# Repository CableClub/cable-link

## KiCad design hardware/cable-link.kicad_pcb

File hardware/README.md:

# Cable-Link Reference Hardware design

## Useful Links

* [Gerber Generation for PCBWay](https://www.pcbway.com/blog/help_center/Generate_Gerber_file_from_Kicad.html)
* [Position Generation for PCBWay](https://www.pcbway.com/blog/help_center/Generate_Position_File_in_Kicad.html)

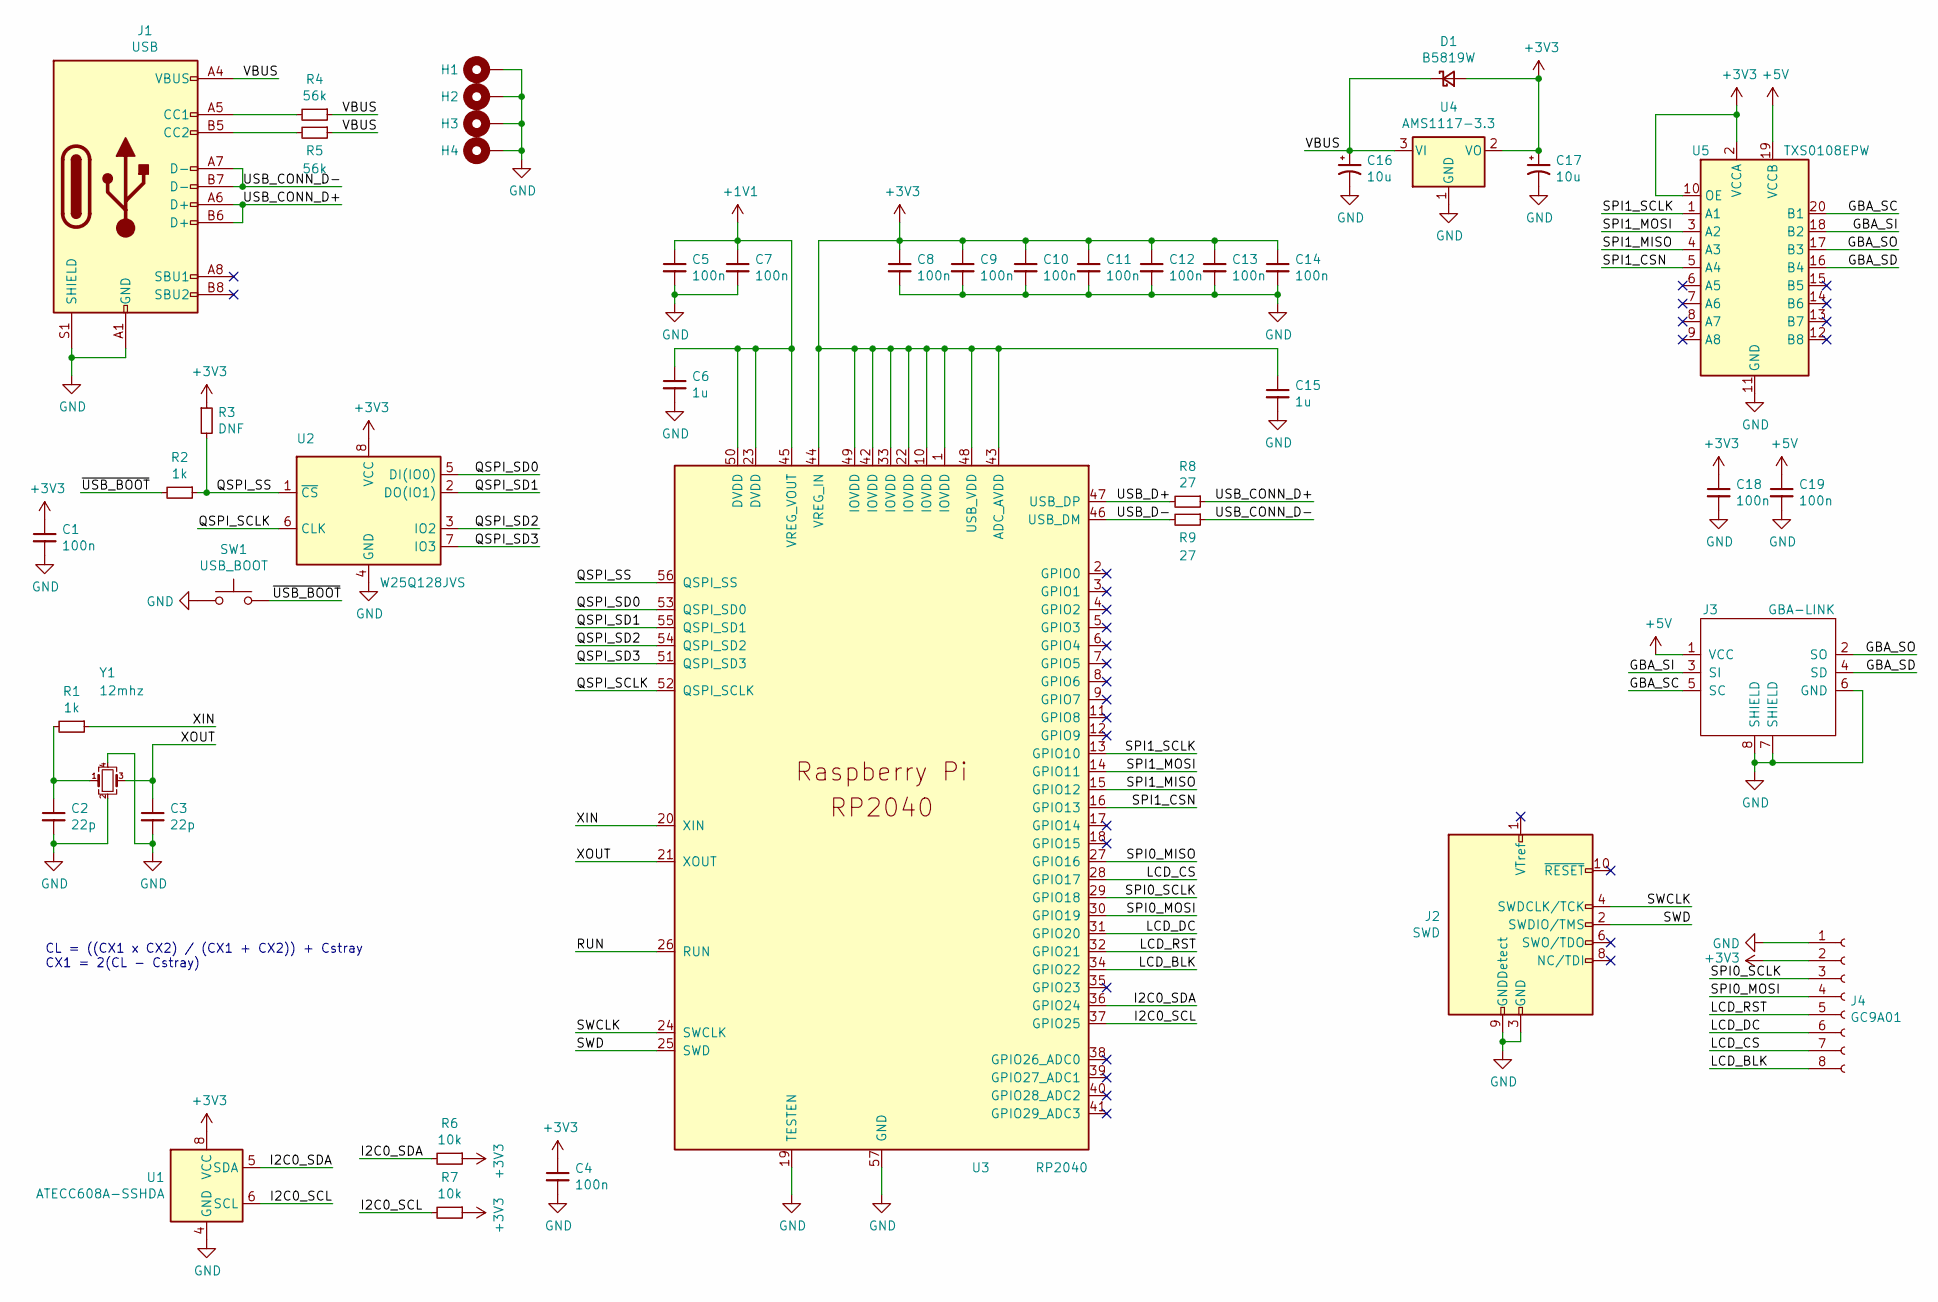
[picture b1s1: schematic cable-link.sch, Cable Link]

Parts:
C1, C4, C5, C7, C8, C9, C10, C11, C12, C13, C14, C18, C19: 100n; C_0402_1005Metric; LCSC_FP 0402
C2, C3: 22p; C_0402_1005Metric; LCSC_FP 0402
C6, C15: 1u; C_0402_1005Metric; LCSC_FP 0402
C16, C17: 10u; CP_EIA-3216-18_Kemet-A; LCSC_FP CASE-A_3216
D1: B5819W; D_SOD-123; LCSC_PN C8598
H1, H2, H3, H4: MountingHole_Pad; MountingHole_2.2mm_M2_DIN965_Pad
J1: USB; TYPE-C-31-M-12; LCSC_FP TYPE-C-31_L8.94_W7.3
J2: SWD; 20021221-00010C4LF
J3: GBA-LINK
J4: GC9A01; PinHeader_1x08_P2.54mm_Vertical
R1, R2: 1k; R_0402_1005Metric; LCSC_FP 0402
R3: DNF; R_0402_1005Metric
R4, R5: 56k; R_0402_1005Metric; LCSC_FP 0402
R6, R7: 10k; R_0402_1005Metric; LCSC_FP 0402
R8, R9: 27; R_0402_1005Metric; LCSC_FP 0402
SW1: USB_BOOT; SW_Push_1P1T_NO_6x6mm_H9.5mm; LCSC_FP SMD-4
U1: ATECC608A-SSHDA; SOIC-8_3.9x4.9mm_P1.27mm; LCSC_FP SOIC-8_3.9x4.9x1.27P
U2: W25Q128JVS; SOIC-8_5.23x5.23mm_P1.27mm; LCSC_FP SOIC-8_5.3x5.3x1.27P
U3: RP2040; RP2040-QFN-56; LCSC_FP LQFN-56_EP_7.0x7.0x0.4P
U4: AMS1117-3.3; SOT-223-3_TabPin2; LCSC_FP SOT-223
U5: TXS0108EPW; TSSOP-20_4.4x6.5mm_P0.65mm; LCSC_FP TSSOP-20_4.4x6.5x0.65P
Y1: 12mhz; Crystal_SMD_3225-4Pin_3.2x2.5mm; LCSC_FP SMD-3225_4P

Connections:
+1V1: C5.1, C6.1, C7.1, U3.23 (DVDD), U3.45 (VREG_VOUT), U3.50 (DVDD)
+3V3: C1.1, C4.1, C8.1, C9.1, C10.1, C11.1, C12.1, C13.1, C14.1, C15.1, C17.1, C18.1, D1.2 (A), J4.2, R3.1, R6.1, R7.1, U1.8 (VCC), U2.8 (VCC), U3.1 (IOVDD), U3.10 (IOVDD), U3.22 (IOVDD), U3.33 (IOVDD), U3.42 (IOVDD), U3.43 (ADC_AVDD), U3.44 (VREG_IN), U3.48 (USB_VDD), U3.49 (IOVDD), U4.2 (VO), U5.2 (VCCA), U5.10 (OE)
+5V: C19.1, J3.1 (VCC), U5.19 (VCCB)
/GBA_SC: J3.5 (SC), U5.20 (B1)
/GBA_SD: J3.4 (SD), U5.16 (B4)
/GBA_SI: J3.3 (SI), U5.18 (B2)
/GBA_SO: J3.2 (SO), U5.17 (B3)
/I2C0_SCL: R7.2, U1.6 (SCL), U3.37 (GPIO25)
/I2C0_SDA: R6.2, U1.5 (SDA), U3.36 (GPIO24)
/LCD_BLK: J4.8, U3.34 (GPIO22)
/LCD_CS: J4.7, U3.28 (GPIO17)
/LCD_DC: J4.6, U3.31 (GPIO20)
/LCD_RST: J4.5, U3.32 (GPIO21)
/QSPI_SCLK: U2.6 (CLK), U3.52 (QSPI_SCLK)
/QSPI_SD0: U2.5 (DI(IO0)), U3.53 (QSPI_SD0)
/QSPI_SD1: U2.2 (DO(IO1)), U3.55 (QSPI_SD1)
/QSPI_SD2: U2.3 (IO2), U3.54 (QSPI_SD2)
/QSPI_SD3: U2.7 (IO3), U3.51 (QSPI_SD3)
/QSPI_SS: R2.1, R3.2, U2.1 (~CS), U3.56 (QSPI_SS)
/RUN: U3.26 (RUN)
/SPI0_MISO: U3.27 (GPIO16)
/SPI0_MOSI: J4.4, U3.30 (GPIO19)
/SPI0_SCLK: J4.3, U3.29 (GPIO18)
/SPI1_CSN: U3.16 (GPIO13), U5.5 (A4)
/SPI1_MISO: U3.15 (GPIO12), U5.4 (A3)
/SPI1_MOSI: U3.14 (GPIO11), U5.3 (A2)
/SPI1_SCLK: U3.13 (GPIO10), U5.1 (A1)
/SWCLK: J2.4 (SWDCLK/TCK), U3.24 (SWCLK)
/SWD: J2.2 (SWDIO/TMS), U3.25 (SWD)
/USB_CONN_D+: J1.A6 (D+), J1.B6 (D+), R8.1
/USB_CONN_D-: J1.A7 (D-), J1.B7 (D-), R9.1
/USB_D+: R8.2, U3.47 (USB_DP)
/USB_D-: R9.2, U3.46 (USB_DM)
/VBUS: C16.1, D1.1 (K), J1.A4 (VBUS), J1.A9 (VBUS), J1.B4 (VBUS), J1.B9 (VBUS), R4.1, R5.1, U4.3 (VI)
/XIN: R1.1, U3.20 (XIN)
/XOUT: C3.1, U3.21 (XOUT), Y1.3
/~USB_BOOT: R2.2, SW1.2
GND: C1.2, C2.2, C3.2, C4.2, C5.2, C6.2, C7.2, C8.2, C9.2, C10.2, C11.2, C12.2, C13.2, C14.2, C15.2, C16.2, C17.2, C18.2, C19.2, H1.1, H2.1, H3.1, H4.1, J1.A1 (GND), J1.A12 (GND), J1.B1 (GND), J1.B12 (GND), J1.S1 (SHIELD), J2.3 (GND), J2.5 (GND), J2.9 (GNDDetect), J3.6 (GND), J3.7 (SHIELD), J3.8 (SHIELD), J4.1, SW1.1, U1.4 (GND), U2.4 (GND), U3.19 (TESTEN), U3.57 (GND), U4.1 (GND), U5.11 (GND), Y1.2, Y1.4
unnamed: C2.1, R1.2, Y1.1
unnamed: J1.A5 (CC1), R4.2
unnamed: J1.B5 (CC2), R5.2

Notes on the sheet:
CL = ((CX1 x CX2) / (CX1 + CX2)) + Cstray CX1 = 2(CL - Cstray)

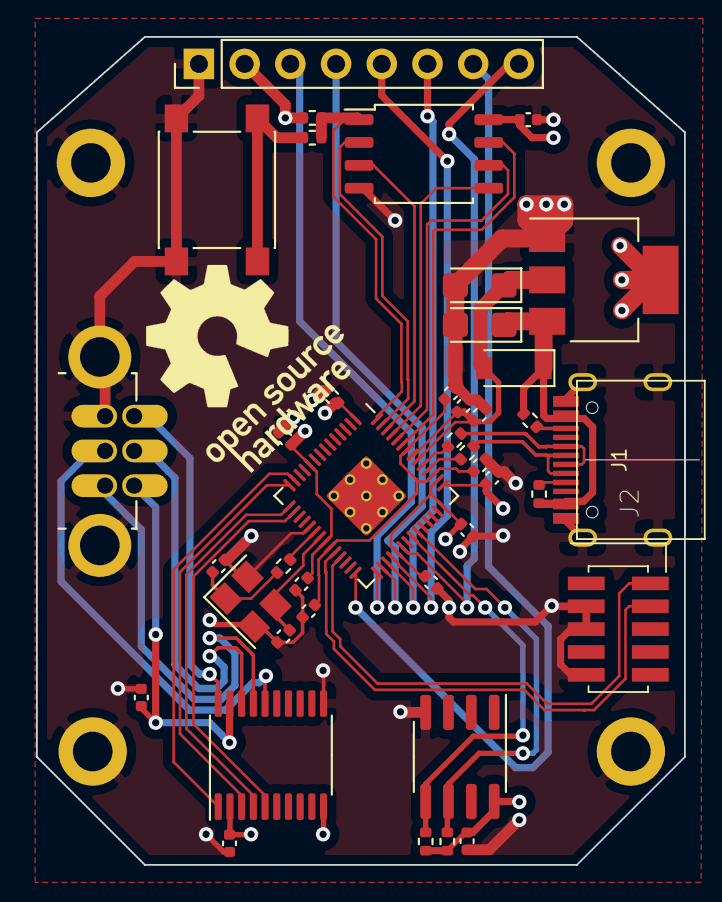
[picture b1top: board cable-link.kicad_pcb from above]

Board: 4 copper layers, 36.0 x 46.0 mm, 44 parts (0 on the bottom side), 39 nets.

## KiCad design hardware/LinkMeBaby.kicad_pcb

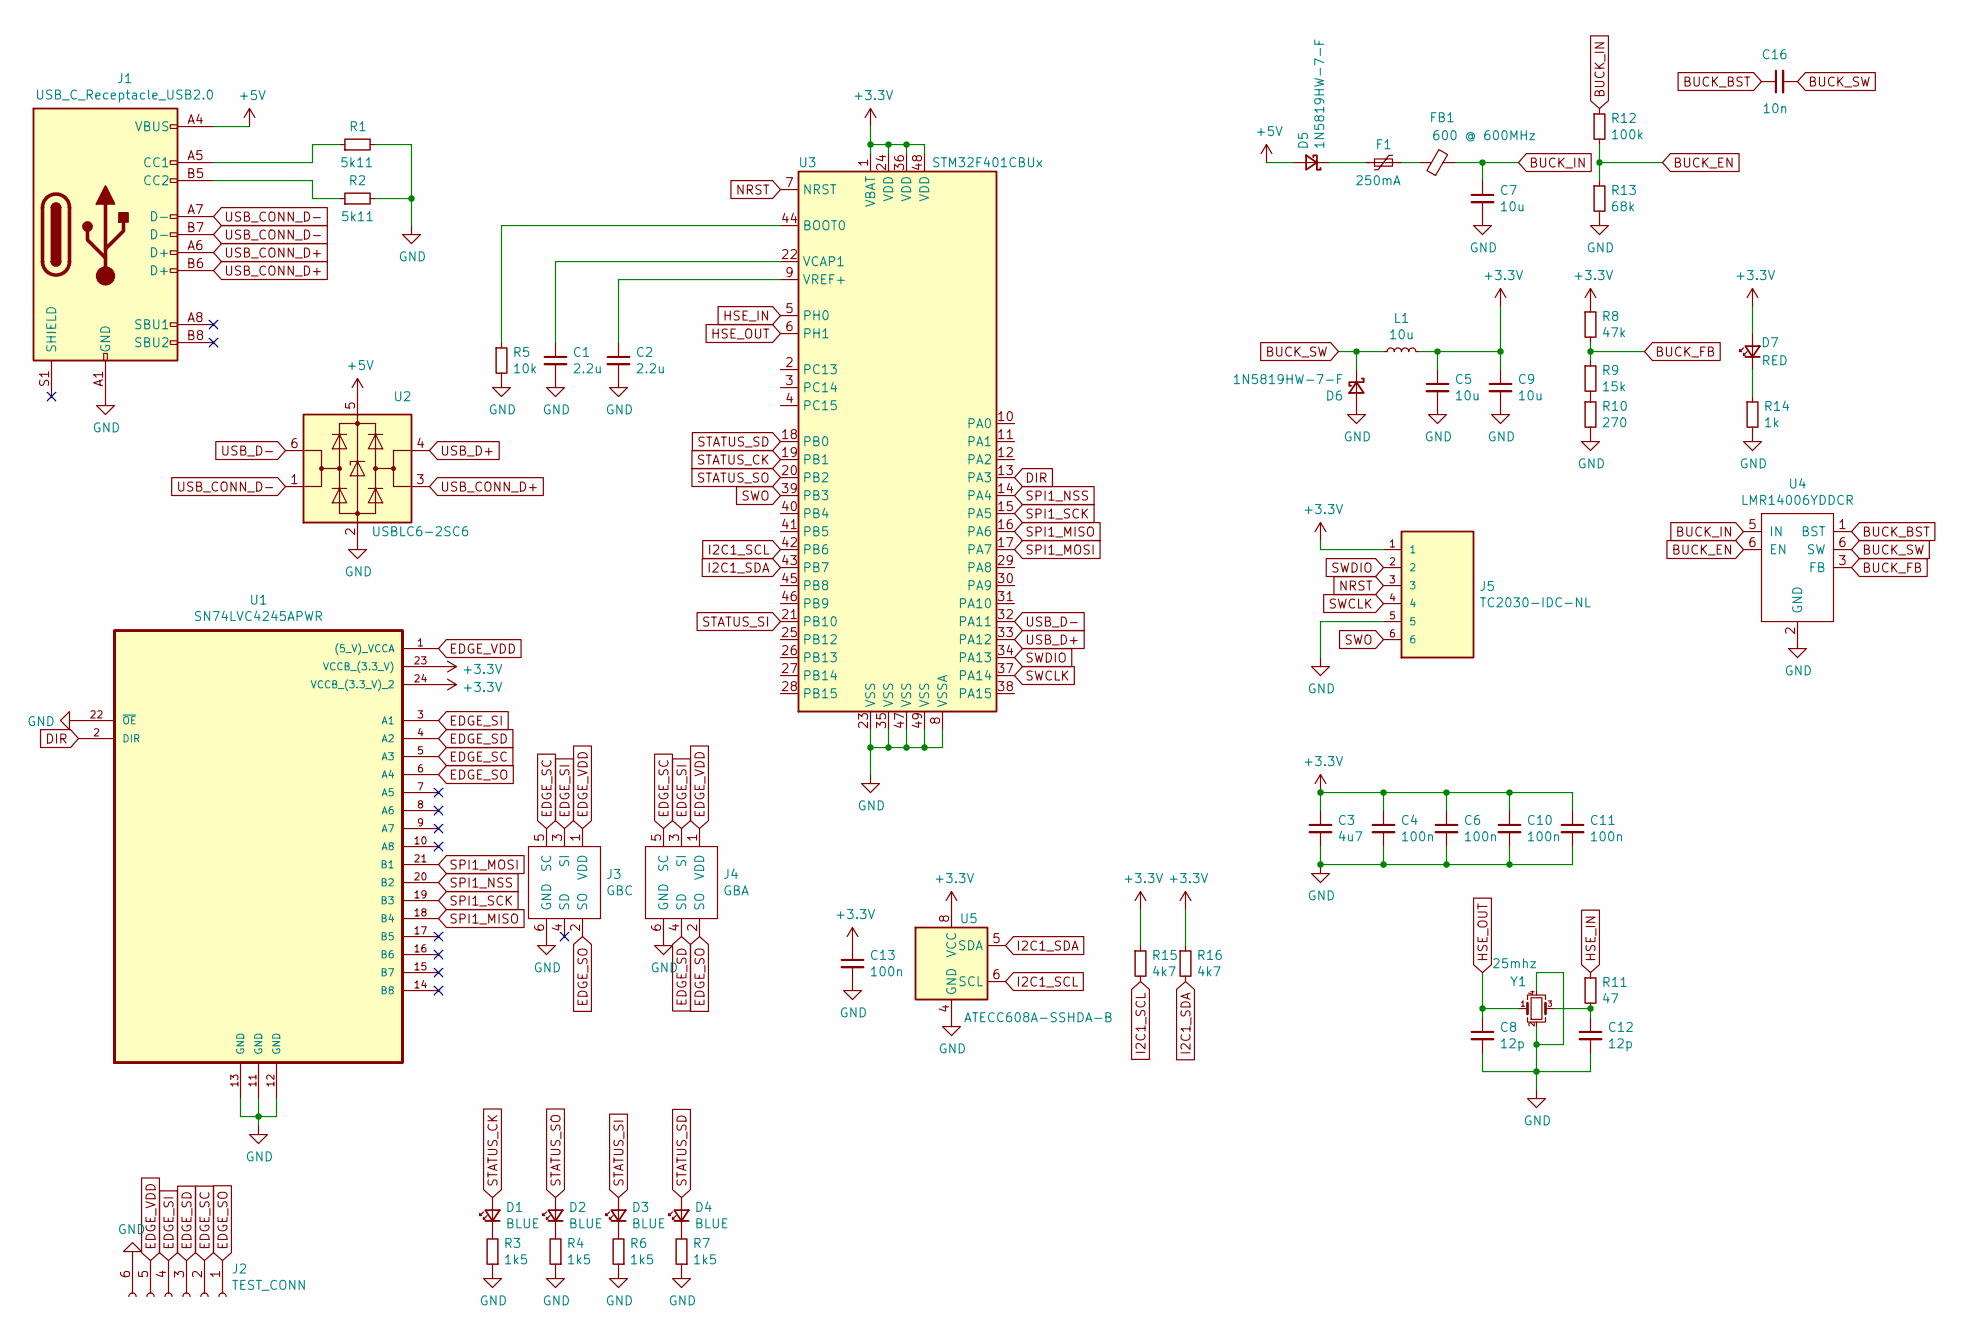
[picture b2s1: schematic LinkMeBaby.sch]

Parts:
C1, C2: 2.2u; C_0201_0603Metric_Pad0.64x0.40mm_HandSolder; LCSC_PN C23630
C3: 4u7; C_0603_1608Metric; LCSC_PN C19666
C4, C6, C10, C11, C13: 100n; C_0402_1005Metric_Pad0.74x0.62mm_HandSolder; LCSC_PN C1525
C5, C7, C9: 10u; C_1206_3216Metric; LCSC_PN C13585
C8, C12: 12p; C_0402_1005Metric_Pad0.74x0.62mm_HandSolder; LCSC_PN C1547
C16: 10n; C_0603_1608Metric; LCSC_PN C57112
D1, D2, D3, D4: BLUE; LED_0603_1608Metric_Pad1.05x0.95mm_HandSolder; LCSC_PN C72041
D5, D6: 1N5819HW-7-F; SOT-23; LCSC_PN C82544
D7: RED; LED_0603_1608Metric_Pad1.05x0.95mm_HandSolder; LCSC_PN C72044
F1: 250mA; Fuse_1206_3216Metric; LCSC_PN C369159
FB1: 600 @ 600MHz; L_0805_2012Metric; LCSC_PN C1017
J1: USB_C_Receptacle_USB2.0; USB_C_Receptacle_HRO_TYPE-C-31-M-12; LCSC_PN C283540
J2: TEST_CONN; PinHeader_1x06_P1.27mm_Vertical
J3: GBC; GBA
J4: GBA
J5: TC2030-IDC-NL; TAG_TC2030-IDC-NL; PARTREV MS
L1: 10u; L_Sunlord_MWSA0518_5.4x5.2mm; LCSC_PN C139506
R1, R2: 5k11; R_0805_2012Metric; LCSC_PN C22843
R3, R4, R6, R7: 1k5; R_0603_1608Metric_Pad0.98x0.95mm_HandSolder; LCSC_PN C25989
R5: 10k; R_0603_1608Metric_Pad0.98x0.95mm_HandSolder; LCSC_PN C22843
R8: 47k; R_0603_1608Metric_Pad0.98x0.95mm_HandSolder; LCSC_PN C25819
R9: 15k; R_0603_1608Metric_Pad0.98x0.95mm_HandSolder; LCSC_PN C22809
R10: 270; R_0603_1608Metric_Pad0.98x0.95mm_HandSolder; LCSC_PN C22966
R11: 47; R_01005_0402Metric_Pad0.57x0.30mm_HandSolder; LCSC_PN C25118
R12: 100k; R_0603_1608Metric_Pad0.98x0.95mm_HandSolder; LCSC_PN C25803
R13: 68k; R_0603_1608Metric_Pad0.98x0.95mm_HandSolder; LCSC_PN C23231
R14: 1k; R_0603_1608Metric_Pad0.98x0.95mm_HandSolder; LCSC_PN C21190
R15, R16: 4k7; R_0402_1005Metric_Pad0.72x0.64mm_HandSolder; LCSC_PN C208992
U1: SN74LVC4245APWR; SOP65P640X120-24N; LCSC_PN C7859
U2: USBLC6-2SC6; SOT-23-6; LCSC_PN C7519
U3: STM32F401CBUx; QFN-48-1EP_7x7mm_P0.5mm_EP5.6x5.6mm; LCSC_PN C118825
U4: LMR14006YDDCR; SOT-23-6; LCSC_PN C477919
U5: ATECC608A-SSHDA-B; SOIC-8_3.9x4.9mm_P1.27mm; LCSC_PN C376619
Y1: 25mhz; Crystal_SMD_3225-4Pin_3.2x2.5mm; LCSC_PN C439049

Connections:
+3V3: C3.1, C4.1, C5.1, C6.1, C9.1, C10.1, C11.1, C13.1, D7.2 (A), J5.1, L1.2, R8.1, R15.1, R16.1, U1.23 (VCCB_(3.3_V)), U1.24 (VCCB_(3.3_V)_2), U3.1 (VBAT), U3.24 (VDD), U3.36 (VDD), U3.48 (VDD), U5.8 (VCC)
+5V: D5.2 (A), J1.A4 (VBUS), J1.A9 (VBUS), J1.B4 (VBUS), J1.B9 (VBUS), U2.5 (VBUS)
BUCK_BST: C16.1, U4.1 (BST)
BUCK_FB: R8.2, R9.1, U4.3 (FB)
BUCK_IN: C7.1, FB1.2, R12.1, U4.5 (IN)
DIR: U1.2 (DIR), U3.13 (PA3)
EDGE_SC: J2.2, J3.5 (SC), J4.5 (SC), U1.5 (A3); also elsewhere on the board
EDGE_SD: J2.3, J4.4 (SD), U1.4 (A2); also elsewhere on the board
EDGE_SI: J2.4, J3.3 (SI), J4.3 (SI), U1.3 (A1); also elsewhere on the board
EDGE_SO: J2.1, J3.2 (SO), J4.2 (SO), U1.6 (A4); also elsewhere on the board
EDGE_VDD: J2.5, J3.1 (VDD), J4.1 (VDD), U1.1 ((5_V)_VCCA); also elsewhere on the board
GND: C1.2, C2.2, C3.2, C4.2, C5.2, C6.2, C7.2, C8.2, C9.2, C10.2, C11.2, C12.2, C13.2, D6.2 (A), J1.A1 (GND), J1.A12 (GND), J1.B1 (GND), J1.B12 (GND), J2.6, J3.6 (GND), J4.6 (GND), J5.5, R1.2, R2.2, R3.1, R4.1, R5.2, R6.1, R7.1, R10.2, R13.2, R14.2, U1.11 (GND), U1.12 (GND), U1.13 (GND), U1.22 (~OE), U2.2 (GND), U3.8 (VSSA), U3.23 (VSS), U3.35 (VSS), U3.47 (VSS), U3.49 (VSS), U4.2 (GND), U5.4 (GND), Y1.2, Y1.4; also elsewhere on the board
HSE_IN: R11.1, U3.5 (PH0)
HSE_OUT: C8.1, U3.6 (PH1), Y1.1
I2C1_SCL: R15.2, U3.42 (PB6), U5.6 (SCL)
I2C1_SDA: R16.2, U3.43 (PB7), U5.5 (SDA)
NRST: J5.3, U3.7 (NRST)
unnamed: C1.1, U3.22 (VCAP1)
unnamed: C2.1, U3.9 (VREF+)
unnamed: C12.1, R11.2, Y1.3
unnamed: D1.1 (K), R3.2
unnamed: D2.1 (K), R4.2
unnamed: D3.1 (K), R6.2
unnamed: D4.1 (K), R7.2
unnamed: D5.1 (K), F1.1
unnamed: D7.1 (K), R14.1
unnamed: F1.2, FB1.1
unnamed: J1.A5 (CC1), R1.1
unnamed: J1.B5 (CC2), R2.1
unnamed: R5.1, U3.44 (BOOT0)
unnamed: R9.2, R10.1
SPI1_MISO: U1.18 (B4), U3.16 (PA6)
SPI1_MOSI: U1.21 (B1), U3.17 (PA7)
SPI1_NSS: U1.20 (B2), U3.14 (PA4)
SPI1_SCK: U1.19 (B3), U3.15 (PA5)
STATUS_CK: D1.2 (A), U3.19 (PB1)
STATUS_SD: D4.2 (A), U3.18 (PB0)
STATUS_SI: D3.2 (A), U3.21 (PB10)
STATUS_SO: D2.2 (A), U3.20 (PB2)
SWCLK: J5.4, U3.37 (PA14)
SWDIO: J5.2, U3.34 (PA13)
SWO: J5.6, U3.39 (PB3)
USB_CONN_D+: J1.A6 (D+), J1.B6 (D+), U2.3 (I/O2)
USB_CONN_D-: J1.A7 (D-), J1.B7 (D-), U2.1 (I/O1)
USB_D+: U2.4 (I/O2), U3.33 (PA12)
USB_D-: U2.6 (I/O1), U3.32 (PA11)

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
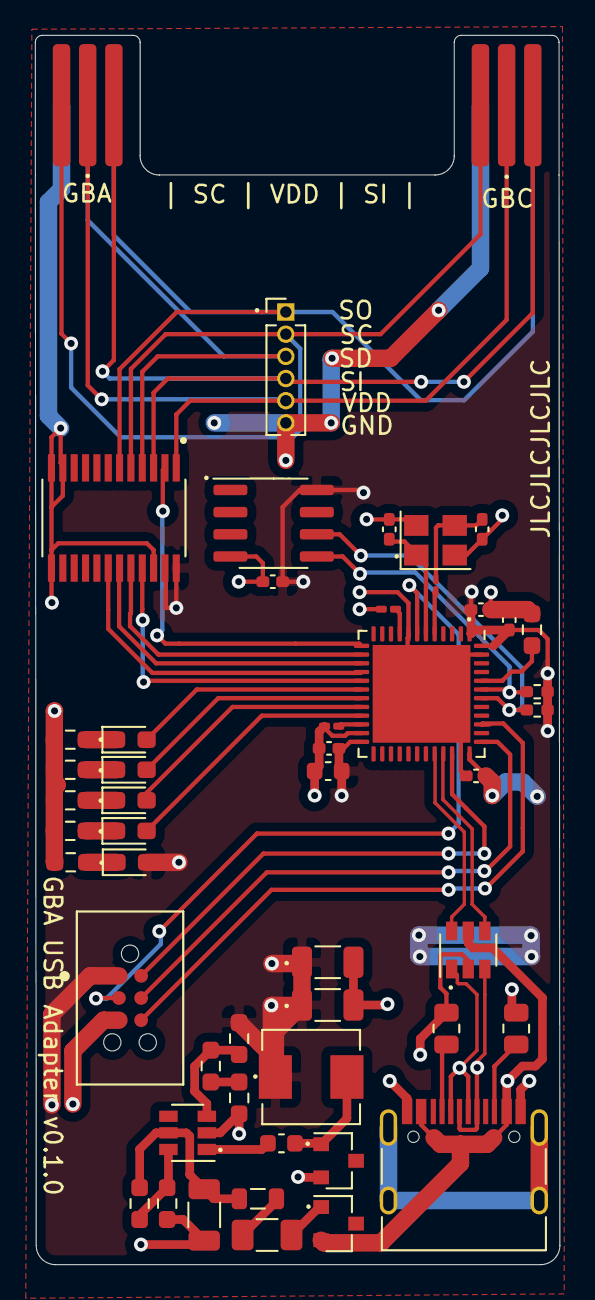
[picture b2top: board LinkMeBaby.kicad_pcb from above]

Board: 2 copper layers, 30.1 x 70.4 mm, 51 parts (0 on the bottom side), 48 nets.

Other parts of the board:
GBA: GBA
GBC: GBC; GBA

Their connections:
EDGE_SC: GBA.5, GBC.5; also elsewhere on the board
EDGE_SD: GBA.4; also elsewhere on the board
EDGE_SI: GBA.3, GBC.3; also elsewhere on the board
EDGE_SO: GBA.2, GBC.2; also elsewhere on the board
EDGE_VDD: GBA.1, GBC.1; also elsewhere on the board
GND: GBA.6, GBC.6; also elsewhere on the board

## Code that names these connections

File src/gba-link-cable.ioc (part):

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PA6.Mode=Full_Duplex_Master
PA7.Mode=Full_Duplex_Master
Mcu.UserName=STM32F401CBUx
PH1\ -\ OSC_OUT.Mode=HSE-External-Oscillator
PA11.Mode=Device_Only
PA3.GPIOParameters=GPIO_Label
PB0.GPIO_Label=STATUS_SD
PA13.Signal=SYS_JTMS-SWDIO
PA12.Signal=USB_OTG_FS_DP
PH0\ -\ OSC_IN.Mode=HSE-External-Oscillator
PH0\ -\ OSC_IN.Signal=RCC_OSC_IN
PA4.Mode=NSS_Signal_Hard_Output
PB10.GPIO_Label=STATUS_SO
PB2.GPIOParameters=GPIO_Label
PB6.Signal=I2C1_SCL
PB6.Mode=I2C
PB10.Signal=GPIO_Output
PA5.Signal=SPI1_SCK
RCC.HSE_VALUE=25000000
PH1\ -\ OSC_OUT.Signal=RCC_OSC_OUT
PB2.Signal=GPIO_Output
PB3.Mode=Trace_Asynchronous_SW
board=custom
PB0.GPIOParameters=GPIO_Label
PA14.Mode=Trace_Asynchronous_SW
PB1.GPIO_Label=STATUS_CK
PB7.Signal=I2C1_SDA
PA13.Mode=Trace_Asynchronous_SW
Mcu.Name=STM32F401C(B-C)Ux
PB3.Signal=SYS_JTDO-SWO
PA4.Signal=SPI1_NSS
RCC.SYSCLKFreq_VALUE=16000000
Mcu.Package=UFQFPN48
PB1.Signal=GPIO_Output
PA6.Signal=SPI1_MISO
PA12.Mode=Device_Only
PB7.Mode=I2C
PA11.Signal=USB_OTG_FS_DM
PA14.Signal=SYS_JTCK-SWCLK
PB2.GPIO_Label=STATUS_SI
PB10.GPIOParameters=GPIO_Label
PB0.Signal=GPIO_Output
PA3.GPIO_Label=DIR
PB1.GPIOParameters=GPIO_Label
PA3.Signal=GPIO_Output
PA5.Mode=Full_Duplex_Master
PA7.Signal=SPI1_MOSI

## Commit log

2021-05-12 LCSC part number hunting
2021-05-12 lol redo the entire thing
2021-05-12 Rename/Move the hardware files
2021-05-12 Cleanup backup files
2021-05-12 Getting close...
2021-05-12 Add test project
2021-05-12 Add README.md
2021-05-13 Add LICENSE
2021-05-28 Switch to pio
    Might change this when the real hardware comes in
2021-05-29 Remove arduino from project
2021-06-17 Start working on a new revision of the hardware
2021-06-17 Finish BOM
2021-06-17 Update BOM tools
2021-06-17 Finish PCB layout
2021-06-17 Submitted and failed review
2021-06-17 Hardware attempt 2
2021-06-27 Hardware Rev. C
    Redesigned the board yet again. Order placed w/ JLCPCB.
2021-06-27 Update render
2021-07-13 Start porting to pico.
    SPI doesn't seem to work Yet. Need to look at it on the scope.
2021-08-24 Almost working
2021-09-06 catchup
